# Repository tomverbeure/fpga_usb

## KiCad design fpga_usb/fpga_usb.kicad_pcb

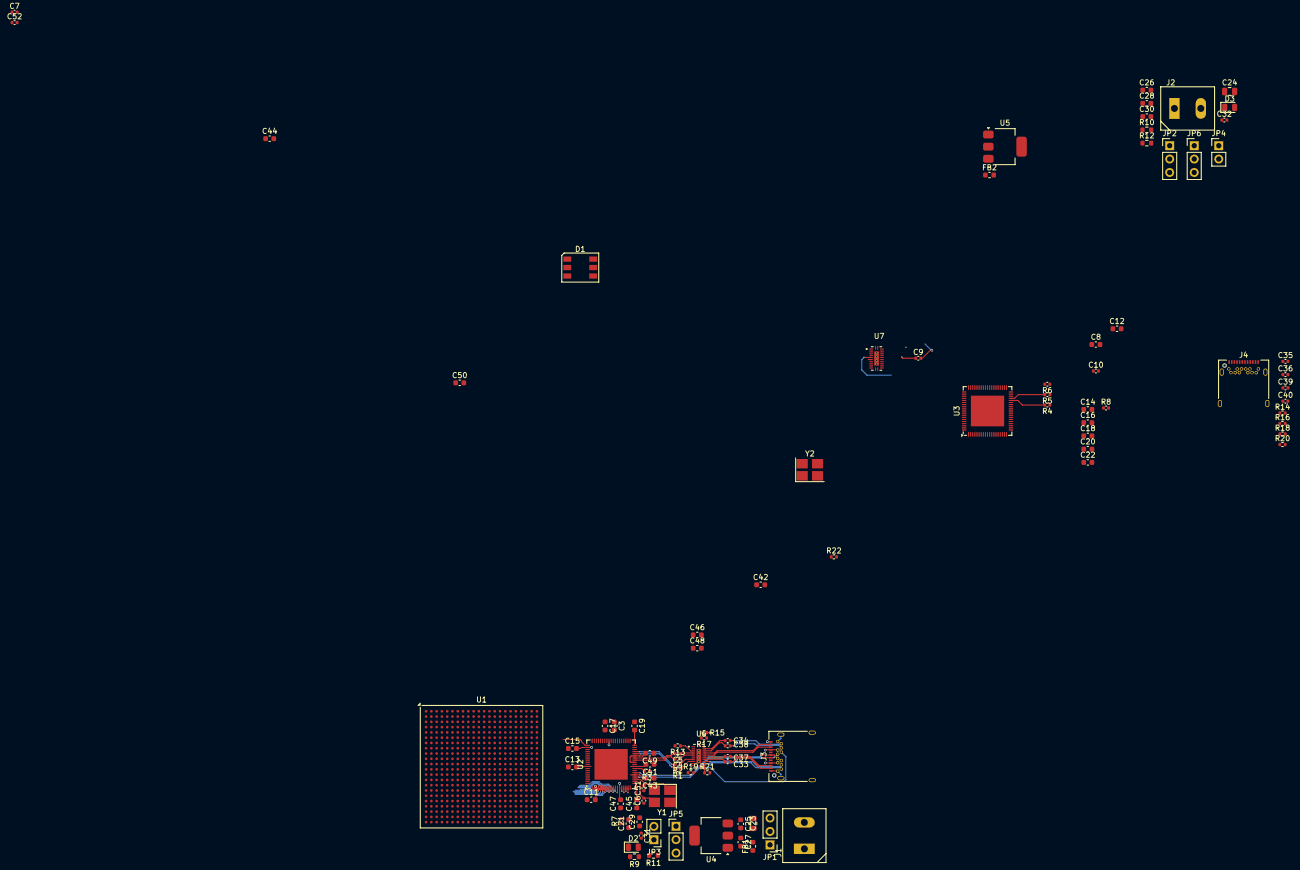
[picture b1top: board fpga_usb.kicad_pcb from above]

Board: 6 copper layers, 96 parts (0 on the bottom side), 89 nets.

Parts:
C3, C8, C11, C12, C13, C14, C15, C16, C17, C18, C19, C20, C25, C26, C27, C28, C41, C42, C43, C44, C45, C46, C47, C48, C49, C50: 470n; C_0603_1608Metric
C4, C5, C9, C10, C31, C32, C33, C34, C35, C36, C37, C38, C39, C40: 100n; C_0402_1005Metric
C6, C7, C51, C52: 3p; C_0402_1005Metric
C21, C22: 100n; C_0603_1608Metric
C23, C24: 10u; C_0805_2012Metric
C29, C30: 47u; C_0603_1608Metric
D1: WS2812S; LED_WS2812_PLCC6_5.0x5.0mm_P1.6mm
D2, D3: LED; LED_0805_2012Metric
FB1, FB2: 28 Ohm / 100MHz; L_0603_1608Metric
J1, J2: Conn_01x02_Pin; TerminalBlock_MAX-MX127-5.0-02P
J3, J4: USB_C_Receptacle; USB_C_Receptacle_Amphenol_12401548E4-2A
JP1, JP2, JP5, JP6: Jumper_3_Open; PinHeader_1x03_P2.54mm_Vertical
JP3, JP4: PWR_MEASURE; PinHeader_1x02_P2.54mm_Vertical
R1, R2, R4, R5: 0; C_0402_1005Metric
R3, R6: 1.6k; C_0402_1005Metric
R7, R8: 10k; C_0402_1005Metric
R9, R10: 360; R_0603_1608Metric
R11, R12: 0; R_0603_1608Metric
R13, R14, R17, R18, R19, R20, R21, R22: 0; R_0402_1005Metric
R15, R16: 1M; R_0402_1005Metric
U1: EP2C35F484; BGA-484_23.0x23.0mm_Layout22x22_P1.0mm
U2, U3: FT601Q; QFN-76-1EP_9x9mm_P0.4mm_EP5.81x6.31mm
U4, U5: AMS1117-3.3; SOT-223-3_TabPin2
U6, U7: PI5USB30213AXEAEX; QFN40P400X200X50-25N
Y1, Y2: X322530MOB4SI; Crystal_SMD_3225-4Pin_3.2x2.5mm_HandSoldering

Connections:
+3.3V: JP5.3 (B), JP6.3 (B)
/FT601_0_CLK: D1.6 (VSS), U2.58 (CLK)
/FT601_0_DATA0: D1.2 (DIN), U2.40 (DATA_0)
/FT601_0_DATA1: D1.1 (DOUT), U2.41 (DATA_1)
/USB0/3V3_LDO: C27.1, JP5.1 (A), U4.2 (VO)
/USB0/5VDC: C23.1, C25.1, FB1.2, U4.3 (VI)
/USB0/5VDC_IN: J1.1, JP1.1 (A)
/USB0/CC1: J3.A5 (CC1), U6.11 (CC1)
/USB0/CC2: J3.B5 (CC2), U6.12 (CC2)
/USB0/DM: J3.A7 (D-), J3.B7 (D-), U2.25 (DM)
/USB0/DP: J3.A6 (D+), J3.B6 (D+), U2.23 (DP)
/USB0/FT601_RESET_N: C21.2, R7.2, U2.15 (~RESET)
/USB0/RIDN: R2.2, U2.35 (RIDP)
/USB0/RIDP: R1.2, U2.34 (RIDN)
/USB0/RX1_N: J3.B10 (RX1-), U6.15 (B1N)
/USB0/RX1_P: J3.B11 (RX1+), U6.14 (B1P)
/USB0/RX2_N: J3.A10 (RX2-), U6.18 (B2N)
/USB0/RX2_P: J3.A11 (RX2+), U6.19 (B2P)
/USB0/RX_N: R2.1, U6.7 (BN)
/USB0/RX_P: R1.1, U6.8 (BP)
/USB0/TODN: C4.2, U2.31 (TODN)
/USB0/TODP: C5.2, U2.32 (TODP)
/USB0/TX1_N: C37.1, J3.A3 (TX1-)
/USB0/TX1_P: C33.1, J3.A2 (TX1+)
/USB0/TX2_N: C38.1, J3.B3 (TX2-)
/USB0/TX2_P: C34.1, J3.B2 (TX2+)
/USB0/TX_N: C4.1, U6.5 (AN)
/USB0/TX_P: C5.1, U6.4 (AP)
/USB0/USB_3V3: C13.2, C15.2, C17.2, C19.2, C29.1, C31.1, C41.2, C43.2, C45.2, C47.2, JP3.2 (B), R7.1, R9.1, R11.2, R19.1, U2.14 (VCCIO), U2.20 (VCC33), U2.24 (VCC33), U2.28 (VDDA), U2.38 (VCC33), U2.49 (VCCIO), U2.59 (VCCIO), U2.68 (VCCIO), U6.6 (VDD)
/USB0/VBUS: J3.A4 (VBUS), J3.A9 (VBUS), J3.B4 (VBUS), J3.B9 (VBUS), JP1.3 (B), R15.2, U2.37 (VBUS)
/USB0/VD10: C3.2, C11.2, C49.2, U2.2 (AVDD), U2.3 (VD10), U2.30 (VD10), U2.33 (VD10), U2.39 (DV10), U2.48 (VD10)
/USB0/XI: C6.2, U2.21 (XI), Y1.3
/USB0/XO: C51.2, U2.22 (XO), Y1.1
/USB1/3V3_LDO: C28.1, JP6.1 (A), U5.2 (VO)
/USB1/5VDC: C24.1, C26.1, FB2.2, U5.3 (VI)
/USB1/5VDC_IN: J2.1, JP2.1 (A)
/USB1/CC1: J4.A5 (CC1), U7.11 (CC1)
/USB1/CC2: J4.B5 (CC2), U7.12 (CC2)
/USB1/DM: J4.A7 (D-), J4.B7 (D-), U3.25 (DM)
/USB1/DP: J4.A6 (D+), J4.B6 (D+), U3.23 (DP)
/USB1/FT601_RESET_N: C22.2, R8.2, U3.15 (~RESET)
/USB1/RIDN: R5.2, U3.35 (RIDP)
/USB1/RIDP: R4.2, U3.34 (RIDN)
/USB1/RX1_N: J4.B10 (RX1-), U7.15 (B1N)
/USB1/RX1_P: J4.B11 (RX1+), U7.14 (B1P)
/USB1/RX2_N: J4.A10 (RX2-), U7.18 (B2N)
/USB1/RX2_P: J4.A11 (RX2+), U7.19 (B2P)
/USB1/RX_N: R5.1, U7.7 (BN)
/USB1/RX_P: R4.1, U7.8 (BP)
/USB1/TODN: C9.2, U3.31 (TODN)
/USB1/TODP: C10.2, U3.32 (TODP)
/USB1/TX1_N: C39.1, J4.A3 (TX1-)
/USB1/TX1_P: C35.1, J4.A2 (TX1+)
/USB1/TX2_N: C40.1, J4.B3 (TX2-)
/USB1/TX2_P: C36.1, J4.B2 (TX2+)
/USB1/TX_N: C9.1, U7.5 (AN)
/USB1/TX_P: C10.1, U7.4 (AP)
/USB1/USB_3V3: C14.2, C16.2, C18.2, C20.2, C30.1, C32.1, C42.2, C44.2, C46.2, C48.2, JP4.2 (B), R8.1, R10.1, R12.2, R20.1, U3.14 (VCCIO), U3.20 (VCC33), U3.24 (VCC33), U3.28 (VDDA), U3.38 (VCC33), U3.49 (VCCIO), U3.59 (VCCIO), U3.68 (VCCIO), U7.6 (VDD)
/USB1/VBUS: J4.A4 (VBUS), J4.A9 (VBUS), J4.B4 (VBUS), J4.B9 (VBUS), JP2.3 (B), R16.2, U3.37 (VBUS)
/USB1/VD10: C8.2, C12.2, C50.2, U3.2 (AVDD), U3.3 (VD10), U3.30 (VD10), U3.33 (VD10), U3.39 (DV10), U3.48 (VD10)
/USB1/XI: C7.2, U3.21 (XI), Y2.3
/USB1/XO: C52.2, U3.22 (XO), Y2.1
GND: C3.1, C6.1, C7.1, C8.1, C11.1, C12.1, C13.1, C14.1, C15.1, C16.1, C17.1, C18.1, C19.1, C20.1, C21.1, C22.1, C23.2, C24.2, C25.2, C26.2, C27.2, C28.2, C29.2, C30.2, C31.2, C32.2, C41.1, C42.1, C43.1, C44.1, C45.1, C46.1, C47.1, C48.1, C49.1, C50.1, C51.1, C52.1, D2.1 (K), D3.1 (K), J1.2, J2.2, J3.A1 (GND), J3.A12 (GND), J3.B1 (GND), J3.B12 (GND), J3.S1 (SHIELD), J4.A1 (GND), J4.A12 (GND), J4.B1 (GND), J4.B12 (GND), J4.S1 (SHIELD), R3.1, R6.1, R13.2, R14.2, R17.2, R18.2, R21.2, R22.2, U2.1 (GND), U2.26 (GND), U2.29 (GND), U2.36 (GND), U2.77 (GND), U3.1 (GND), U3.26 (GND), U3.29 (GND), U3.36 (GND), U3.77 (GND), U4.1 (GND), U5.1 (GND), U6.25 (GND), U7.25 (GND), Y1.2, Y1.4, Y2.2, Y2.4
unnamed: D2.2 (A), R9.2
unnamed: D3.2 (A), R10.2
unnamed: FB1.1, JP1.2 (C)
unnamed: FB2.1, JP2.2 (C)
unnamed: JP3.1 (A), JP5.2 (C), R11.1
unnamed: JP4.1 (A), JP6.2 (C), R12.1
unnamed: R3.2, U2.27 (RREF)
unnamed: R6.2, U3.27 (RREF)
unnamed: C33.2, U6.16 (A1P)
unnamed: C38.2, U6.20 (A2N)
unnamed: C34.2, U6.21 (A2P)
unnamed: R17.1, U6.22 (ADDR)
unnamed: C37.2, U6.17 (AIN)
unnamed: R21.1, U6.13 (ENB)
unnamed: R13.1, U6.3 (PORT)
unnamed: R15.1, U6.23 (VBUSDET)
unnamed: R19.2, U6.10 (VCONN)
unnamed: C35.2, U7.16 (A1P)
unnamed: C40.2, U7.20 (A2N)
unnamed: C36.2, U7.21 (A2P)
unnamed: R18.1, U7.22 (ADDR)
unnamed: C39.2, U7.17 (AIN)
unnamed: R22.1, U7.13 (ENB)
unnamed: R14.1, U7.3 (PORT)
unnamed: R16.1, U7.23 (VBUSDET)
unnamed: R20.2, U7.10 (VCONN)

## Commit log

2025-03-30 USB section.
2025-03-30 Import USB3 switch. Narrow Netclass.
2025-03-31 First placement trial of USB0.
